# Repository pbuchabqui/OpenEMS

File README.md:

# OpenEMS

ECU para motores a combustao interna, focada no STM32H562RGT6 (Cortex-M33, C++17). Prioriza baixa latencia, baixo jitter e previsibilidade temporal para injecao, ignicao, sensores e calibracao.

Regras de codigo, gates de qualidade e errata: ver `CLAUDE.md`.

## Build

```bash
make firmware     # .elf/.hex/.bin em /tmp/openems-build
make host-test    # regressao no PC
make ci-local     # todos os gates antes de merge
make clean
```

## Instalacao no motor

Pelo dashboard proprio (`tools/openems_dash`, aba **Install**), com guia passo a passo; alternativa: TunerStudio com `tools/ts/openems.ini`.

## Documentacao

| Documento | Conteudo |
|---|---|
| `docs/bench_test_manual.md` | Teste de bancada na WeAct VGT6, sem atuadores |
| `docs/bench_report_template.md` | Modelo do relatório de bancada (preencher durante o ensaio) |
| `docs/hw/README.md` | Hardware e pinout |
| `docs/wiring_diagram.md` | Esquematicos eletricos |
| `docs/ROADMAP.md` | Backlog, progresso e histórico do que foi concluído |
| `docs/datalog.md` | Datalog em cartão SD (VGT6): formato, anel e ferramentas |
| `docs/nn_viabilidade.md` | Estudo: redes neurais no STM32H562 (X-τ, STFT, PID) |
| `docs/guia_instalacao.md` | Guia de instalação no motor (10 passos) |
| `docs/arquitetura.md` | Camadas, regras e contratos entre elas |
| `docs/pipeline_motor.md` | Captura CKP/CMP, combustível, ignição, scheduling, ADC, comunicação |
| `docs/errata_stm32h562.md` | Errata ES0565 e impactos no projeto |
| `docs/qualidade_e_testes.md` | Gates locais, layout dos testes host, segredos |
| `docs/mvp_bancada.md` | Definição de pronto da bancada, frames CAN, ETB, X-τ |
| `docs/estado_e_hardening.md` | Estado atual, hardening feito e pinout por placa |
| `docs/fueling_system.md`, `closed_loop_fuel.md`, `idle_system.md`, `ignition_system.md`, `protection_system.md`, `output_contract.md` | Subsistemas |

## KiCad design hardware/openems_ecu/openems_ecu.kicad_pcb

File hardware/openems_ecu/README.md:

# OpenEMS ECU — KiCad (fork mRE) — ⛔ CONGELADO

> **Não editar. Não é a board de produção.** Desde **2026-08-07** o desenho de produção
> é [`hardware/openems_v1/`](../openems_v1/), um projecto KiCad em branco.
> Porquê da mudança: [`docs/hw/microruseefi_as_base.md`](../../docs/hw/microruseefi_as_base.md).
>
> Isto fica por dois motivos: é o **recuo** se o desenho novo encalhar, e guarda as libs
> verificadas em `rusefi_lib/` (`tle8888qk.lib`, Net-Tie, AMPSEAL) que a board nova reutiliza.
>
> Estado em que ficou: DRC **nunca passou**, 2 camadas de sinal (a v1 pede 4), e restam
> nets fantasma do mRE (ex. `/PE1`, que no H562 LQFP100 é VCAP).

Cópia de trabalho a partir de [rusefi/hw_microRusEfi](https://github.com/rusefi/hw_microRusEfi),
adaptada ao firmware OpenEMS (**STM32H562VGT6** + **TLE8888-2QK**).

## Abrir

```bash
kicad hardware/openems_ecu/openems_ecu.kicad_pro
```

## Sheets

| Ficheiro | Função |
|----------|--------|
| `openems_ecu.kicad_sch` | Raiz hierárquica |
| `openems_ecu.kicad_pcb` | Layout (base mRE + rework H562) |
| `mcu_h562.kicad_sch` | MCU **STM32H562VGTx** LQFP100 (activo) |
| `stm32.kicad_sch` | Arquivo F407 — **não** está na hierarquia |
| `TLE8888-1QK.kicad_sch` | Hub TLE8888 |
| `TLE9201SG.kicad_sch` | ETB H-bridge mRE |
| `adc.kicad_sch` | Entradas analógicas |
| `hi-lo.kicad_sch` | USB / níveis |
| `pair.kicad_sch` | Low-sides (×2) |
| `FlashMemory.kicad_sch` | Flash opcional |

## Libs

| Caminho | Uso |
|---------|-----|
| `rusefi_lib/` | Símbolos legacy mRE (TLE, molex, …) |
| `rusefi_lib_external/` | Footprints / libs estendidas |
| `hellen-one` → `../vendor/hw_microRusEfi/hellen-one` | Footprint USB mini-B |

```bash
# Se libs faltarem após clone limpo:
git submodule update --init --recursive hardware/vendor/hw_microRusEfi
# rsync opcional a partir do vendor se rusefi_lib_external estiver incompleto
```

## Estado OpenEMS

1. ~~MCU H562 sheet~~ ✅ `mcu_h562.kicad_sch`, INJEN=`PE14`
2. ~~Rework 6 pads no PCB~~ ✅ VCAP×2, VDDUSB, VSSA/VSS; enables TLE→PE14/PE3
3. Auditoria TLE vs `docs/hw/tle8888_pinout.md`
4. Conector AMPSEAL 35+23 vs 48-pin mRE (aberto)
5. ETB TLE9201 vs BTS7960 (aberto)
6. DRC / refill zones / Gerber

Arquitectura: [`docs/hw/microruseefi_as_base.md`](../../docs/hw/microruseefi_as_base.md).

## Créditos

Hardware base © rusEFI / microRusEFI contributors.

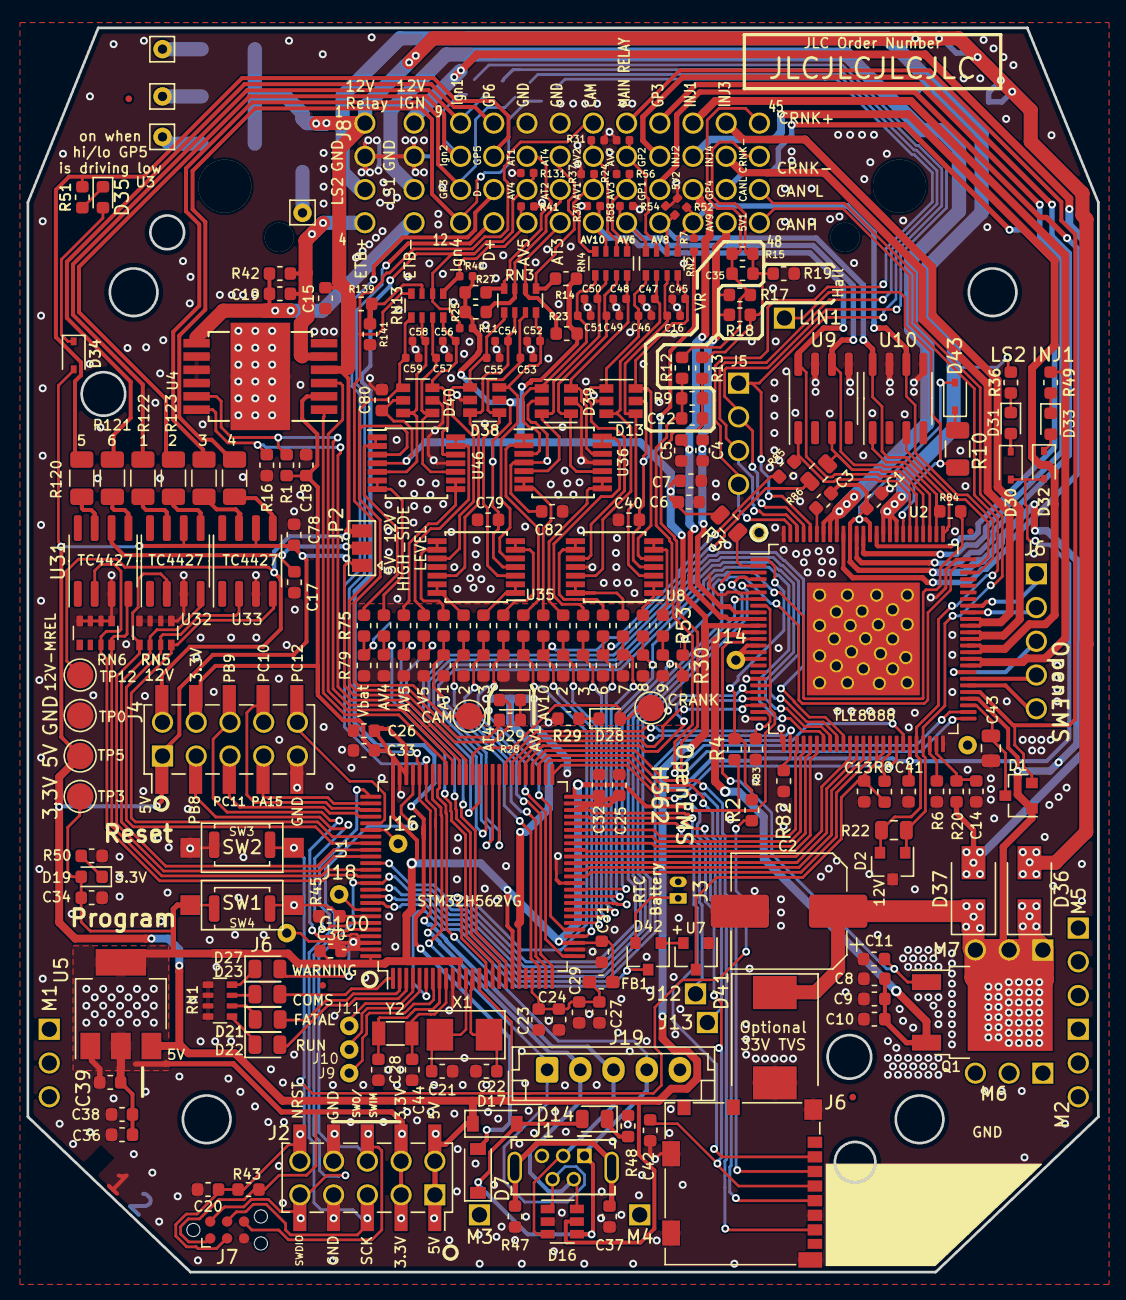
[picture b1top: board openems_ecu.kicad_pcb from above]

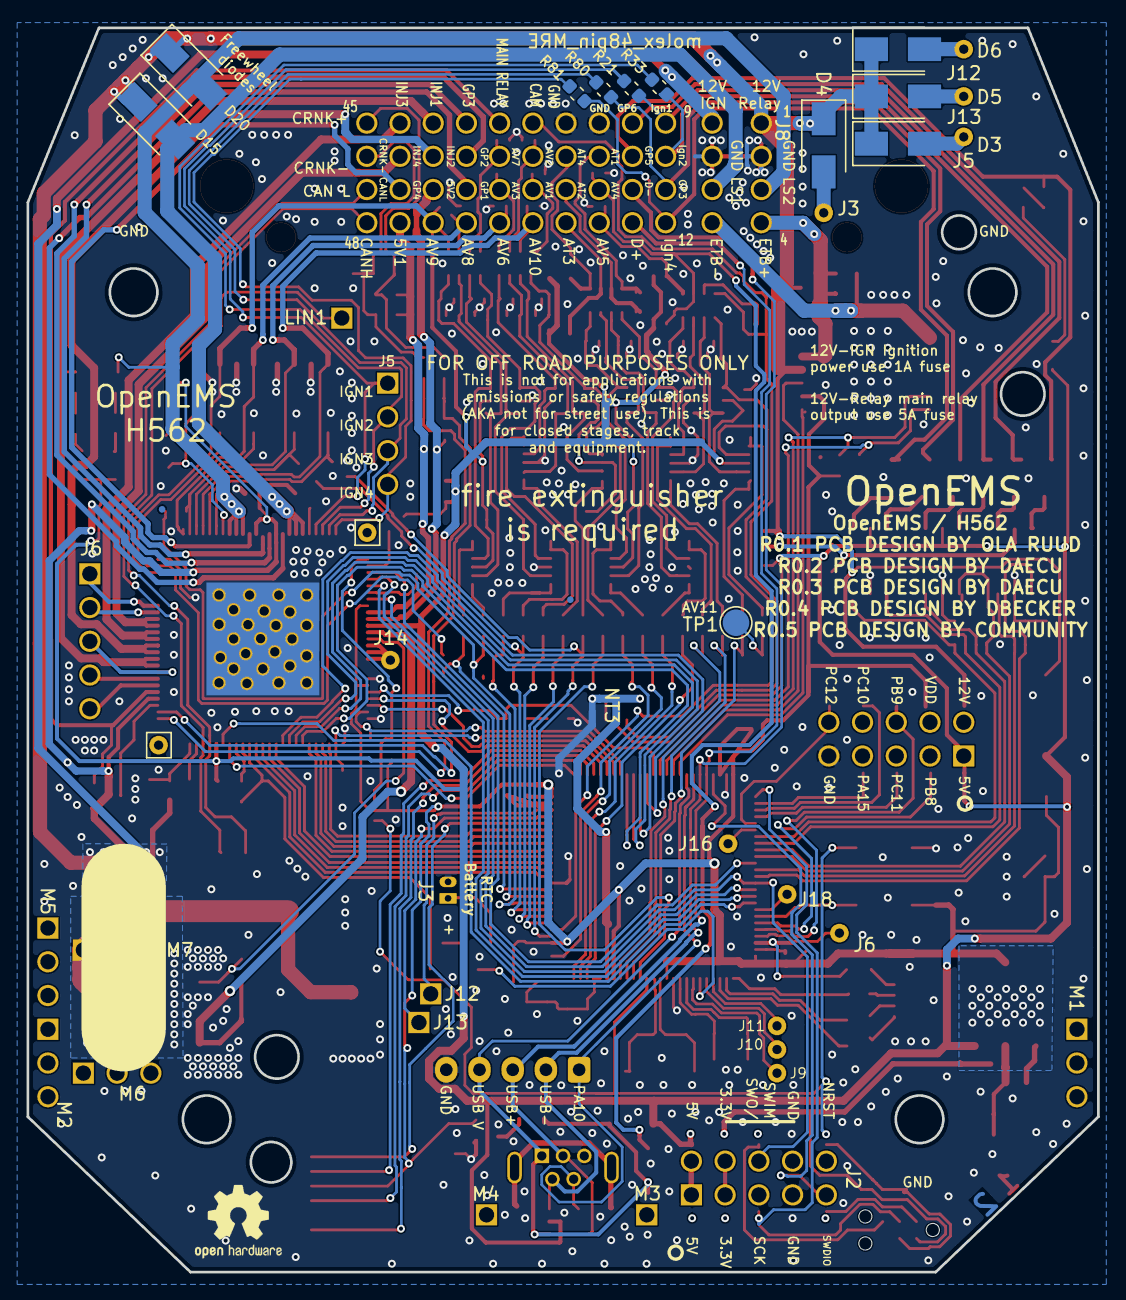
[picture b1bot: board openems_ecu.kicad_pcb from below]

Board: 2 copper layers, 80.6 x 93.7 mm, 254 parts (18 on the bottom side), 223 nets.

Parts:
C1, C6, C10, C13, C14, C15, C17, C18, C24, C30, C31, C32, C33, C34, C37, C38, C42, C78: 100nF; C_0603_1608Metric
C2: 100UF 50V; CP_Elec_8x10.5
C3, C11: 4.7nF; C_0603_1608Metric
C4, C5: 470nF; C_0603_1608Metric
C7, C8, C9: 10uF; C_0603_1608Metric
C12, C35: 1nF; C_0603_1608Metric
C16, C45, C46, C47, C48, C49, C50, C51, C52, C53, C54, C55, C56, C57, C58, C59: 100nF; C_0402_1005Metric
C19, C20, C29, C40, C79, C80, C82: 10nF; C_0603_1608Metric
C21, C22: 18pF; C_0603_1608Metric
C23, C27, C36: 1uF; C_0603_1608Metric
C25, C26, C41, C100: 2.2uF; C_0603_1608Metric
C28, C44: 6.8pF; C_0603_1608Metric
C39: 22uF; C_0603_1608Metric
C43: 22uF 25V; C_0805_2012Metric
D1, D42: BAV70; SOT-23
D2: PESD1CAN-UX; SOT-23
D3, D4, D5, D6, D15, D20, D36, D37: SS54; D_SMA
D7, D17: B5819W; D_SOD-123
D13, D16, D38, D39, D40: SRV05-4; SOT-23-6
D14, D22: LED-GREEN; LED_0805_2012Metric
D19, D28, D29, D31, D33, D35: LED-RED; LED_0603_1608Metric
D21: LED-RED; LED_0805_2012Metric
D23: LED-BLUE; LED_0805_2012Metric
D27: LED-YELLOW; LED_0805_2012Metric
D30, D32, D34, D43: 1N4148WS; D_SOD-323
D41: SM15T33C; D_SMC
FB1: FILTER; R_0603_1608Metric_Pad1.05x0.95mm_HandSolder
FID1, FID2, FID3, FID4, FID5, FID6: Fiducial; Fiducial_0.5mm_Mask1mm
G1: Disclaimer; Off_Road_Disclaimer
J1: USB_B_Mini; USB-MINI-B-VERTICAL
J2: Conn_02x05_Odd_Even; PinSocket_2x05_P2.54mm_Vertical_SMD
J3, J5, J12, J13, J15, J17: Conn_01x01; Pin_D0.7mm_L6.5mm_W1.8mm_FlatFork
J4: Conn_02x05_Counter_Clockwise; PinHeader_2x05_P2.54mm_Vertical_SMD
J6: Micro_SD_Card_Det; microSD_HC_Molex_104031-0811
J7: TC2030; Tag-Connect_TC2030-IDC-NL_2x03_P1.27mm_Vertical
J19: Conn_01x06; JST_EH_B5B-EH-A_1x05_P2.50mm_Vertical
JP2: High side voltage 5V 12V; SolderJumper-3_P1.3mm_Open_Pad1.0x1.5mm
LOGO1: DNP; OSHW-Logo2_7.3x6mm_SilkScreen
NT1, NT2: Net-Tie_2; Net-Tie_2_8.5mil
NT3: Analog Ground Net Tie; NetTie-2_SMD_Pad0.5mm
Q1: IPD30N06S2L-23; TO-252-2
R1, R4, R6, R12, R13, R16, R38, R39, R43, R44, R45, R46, R60, R61, R62, R63, R68, R69, R70, R71, R76, R77, R78, R79, R141: 10K; R_0603_1608Metric
R2: 0R DNP; R_0603_1608Metric
R3: 10K; R_0805_2012Metric
R5, R26, R32, R35, R53, R55, R57, R59, R64, R65, R66, R67, R72, R73, R74, R75: 6.8K; R_0603_1608Metric
R7, R11, R40: DNP; R_0402_1005Metric
R8, R21, R30, R33, R80, R81, R84, R85: 0R; R_0603_1608Metric
R9, R42, R82, R83: 4.7K; R_0603_1608Metric
R10: 1k; R_1206_3216Metric
R14, R20, R23, R25, R27: 2.7k; R_0603_1608Metric
R15, R17, R18, R19: DNP; R_0603_1608Metric
R22: 120; R_0805_2012Metric
R24, R31, R34, R37, R41, R52, R54, R56, R58, R131: 470K; R_0402_1005Metric
R28, R48: 2.2k; R_0603_1608Metric
R29, R36, R49, R50, R51: 1k; R_0603_1608Metric
R47: 100K; R_0603_1608Metric
R86: 0R; R_0805_2012Metric
R120, R121, R122, R123, R124, R125: 100; R_1206_3216Metric
R139: 39k; R_0603_1608Metric
RN1: 1k; R_Array_Convex_4x0603
RN2, RN3, RN4, RN5, RN6, RN13: 10k; R_Array_Convex_4x0603
SW1, SW2: SW_Push; SW_SPST_CK_RS282G05A3
SW3, SW4: SW_Push; SW_Push_SPST_NO_Alps_SKRK
TP0, TP3: GND; TestPoint_Pad_D2.0mm
TP1, TP2, TP4: TP; TestPoint_Pad_D2.0mm
TP5, TP12: 5V; TestPoint_Pad_D2.0mm
U1: STM32H562VGT6; LQFP-100_14x14mm_P0.5mm
U2: TLE8888QK; LQFP-100_14x14mm_P0.5mm_THERMAL
U3: molex_48pin_MRE; Molex_48_MRE
U4: TLE9201SG; Infineon_PG-DSO-12-11
U5: LM1117-3.3; SOT-223-3_TabPin2
U7: XC6206 3.3V; SOT-23
U8, U35, U36, U46: MCP6004; TSSOP-14_4.4x5mm_P0.65mm
U9, U10: VNLD5090; SO-8_3.9x4.9mm_P1.27mm
U31, U32, U33: MIC4427; SOIC-8_3.9x4.9mm_P1.27mm
X1: 8MHz 20pF; Crystal_SMD_5032-2Pin_5.0x3.2mm
Y2: 32768 Hz; Crystal_SMD_3215-2Pin_3.2x1.5mm

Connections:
/5V: C6.1, C7.1, C40.1, C41.1, C78.1, C79.1, C80.1, C82.1, D13.5, D16.5, D17.1 (K), D29.2 (A), D30.2 (A), D32.2 (A), D34.2 (A), D38.5, D39.5, D40.5, J2.1, J2.2, J4.1, JP2.1 (A), R3.2, R7.1, R11.2, R14.2, R23.2, R25.2, R27.2, R40.2, TP5.1, U2.11 (V5V), U2.45 (V5V_CAN), U3.J201, U3.J202, U3.J801, U5.3 (VI), U8.4 (V+), U32.6 (V+), U33.6 (V+), U35.4 (V+), U36.4 (V+), U46.4 (V+)
/5V1: C4.1, R17.1, R18.1, U2.9 (T5V1), U3.44
/5V2: C5.1, U2.10 (T5V2), U3.39
/12V_KEY: D37.2 (A), R20.2, U3.5
/12V_MREL: C15.1, D3.1 (K), D4.1 (K), D5.1 (K), D6.1 (K), D15.1 (K), D20.1 (K), D36.2 (A), J4.2, JP2.3 (B), R139.2, TP12.1, U3.1, U3.J802, U4.4 (VS)
/12V_SAFE: C1.1, C2.1, C3.1, D1.1 (A), D36.1 (K), D37.1 (K), D41.1 (A1), D43.2 (A), Q1.2 (D), U2.54 (BAT), U2.87 (BAT_PA), U2.90 (BAT_PB), U3.M71, U3.M72, U3.M73
/ADC/AGND: NT3.2, R38.1, R39.1, R44.1, R46.1, R60.1, R61.1, R62.1, R63.1, R68.1, R69.1, R70.1, R71.1, R76.1, R77.1, R78.1, R79.1, U1.20 (VSSA)
/ADC/AV11_MCU: R75.1, R79.2, TP1.1
/AT1: R27.1, RN3.4 (R4.1), U3.18
/AT1_MCU: R67.1, R71.2, U1.23 (PA0)
/AT2: R25.1, RN3.3 (R3.1), U3.23
/AT2_MCU: R66.1, R70.2, U1.24 (PA1)
/AT3: R23.1, RN3.2 (R2.1), U3.24
/AT3_MCU: R65.1, R69.2, U1.25 (PA2)
/AT4: R14.1, RN3.1 (R1.1), U3.22
/AT4_MCU: R64.1, R68.2, U1.26 (PA3)
/AV1: R37.1, RN4.4 (R4.1), U3.27
/AV1_MCU: R35.1, R46.2, U1.15 (PC0)
/AV2: R31.1, RN4.2 (R2.1), U3.26
/AV2_MCU: R26.1, R39.2, U1.31 (PA6)
/AV3: R24.1, RN4.1 (R1.1), U3.31
/AV3_MCU: R5.1, R38.2, U1.32 (PA7)
/AV4: D7.2 (A), R11.1, R131.1, RN13.2 (R2.1), U3.19
/AV4_MCU: R73.1, R77.2, U1.17 (PC2)
/AV5: R40.1, R41.1, RN13.1 (R1.1), U3.20
/AV5_MCU: R72.1, R76.2, U1.18 (PC3)
/AV6: R58.1, RN2.4 (R4.1), U2.78 (DFB_12), U3.32, U9.6 (D2)
/AV6_MCU: R59.1, R63.2, R86.2, U1.33 (PC4)
/AV7: R56.1, RN2.3 (R3.1), U3.30
/AV7_MCU: R57.1, R62.2, U1.34 (PC5)
/AV8: R54.1, RN2.2 (R2.1), U2.76 (DFB_11), U3.36, U10.8 (D1)
/AV8_MCU: R55.1, R61.2, R84.2, U1.35 (PB0)
/AV9: R7.2, R52.1, RN2.1 (R1.1), U2.73 (DFB10), U3.40, U10.6 (D2)
/AV9_MCU: R30.2, R53.1, R60.2, U1.36 (PB1)
/AV10: R34.1, RN4.3 (R3.1), U2.80 (DFB_13), U3.28, U9.8 (D1)
/AV10_MCU: R32.1, R44.2, R85.2, U1.29 (PA4)
/CAM_MCU: C59.1, D40.4, RN13.5 (R4.2), TP2.1, U1.30 (PA5), U46.3 (+)
/CAM_SENSOR: R28.1, RN13.4 (R4.1), U3.25
/CANH: D2.2 (C2), R22.1, U2.46 (CAN_H), U3.48
/CANL: D2.1 (C1), R22.2, U2.47 (CAN_L), U3.47
/CRANK: D28.2 (A), TP4.1, U1.63 (PC6), U2.21 (VR_OUT)
/CRNK+: C35.1, R12.1, R15.1, R17.2, U3.45
/CRNK-: C35.2, R13.1, R15.2, R18.2, R19.2, U3.46
/CS_TLE: U1.86 (PD5), U2.3 (CSN)
/E-THROTTLE+: C19.2, R42.2, U3.4, U4.5 (OUT1)
/E-THROTTLE-: C19.1, R42.1, U3.8, U4.7 (OUT2)
/FlashMemory/CS: J6.2 (DAT3/CD), U1.46 (PE15)
/FlashMemory/SCK: J6.5 (CLK), U1.52 (PB13)
/FlashMemory/SI: J6.3 (CMD), U1.54 (PB15)
/FlashMemory/SO: J6.7 (DAT0), U1.53 (PB14)
/GP1: U2.91 (OUT_21), U3.35
/GP2: U2.89 (OUT_22), U3.34
/GP3: U2.88 (OUT_23), U3.33
/GP4: U2.86 (OUT_24), U3.43
/GP5: R51.2, R120.1, U3.14
/GP6: R121.1, U3.13
/H-BRIDGE/DIR: U1.67 (PA8), U4.1 (DIR)
/H-BRIDGE/DIS: R1.2, U1.65 (PC8), U4.11 (DIS)
/H-BRIDGE/PWM: R16.1, U1.64 (PC7), U4.12 (PWM)
/H-BRIDGE/SO: U1.66 (PC9), U4.3 (SO)
/INJECTOR-1: R49.2, U2.59 (OUT_1A), U2.60 (OUT_1B), U3.37
/INJECTOR-2: U2.61 (OUT_2A), U2.62 (OUT_2B), U3.38
/INJECTOR-3: U2.63 (OUT_3A), U2.64 (OUT_3B), U3.41
/INJECTOR-4: U2.65 (OUT_4A), U2.66 (OUT_4B), U3.42
/Ign1: R21.1, R122.1, U3.9
/Ign2: R33.1, R123.1, U3.10
/Ign3: R80.1, R124.1, U3.11
/Ign4: R81.1, R125.1, U3.12
/LINBUS: R10.2, U2.82 (LIN_IO), U3.LIN1
/LS1: D15.2 (A), U2.92 (OUT_6A), U2.93 (OUT_6B), U2.94 (OUT_6C), U3.7
/LS2: D20.2 (A), R36.2, U2.83 (OUT_5A), U2.84 (OUT_5B), U2.85 (OUT_5C), U3.3
/MAIN_RELAY: D1.2 (A), U2.55 (MR), U3.29
/MCU/BOOT0: R45.1, SW1.2, SW4.2, U1.94 (BOOT0)
/MCU/PA9: D7.1 (K), D14.2 (A), D16.4, D17.2 (A), J1.1 (VBUS), J19.4, NT1.2
/MCU/PA10: D16.1, J1.4 (ID), J19.1, U1.69 (PA10)
/MCU/PA13: J2.9, J7.2, U1.72 (PA13), U3.J209
/MCU/PA14: J2.5, J7.4, U1.76 (PA14), U3.J205
/MCU/PB2-BOOT1: NT2.2, U1.37 (PB2)
/MCU/PB6: U1.92 (PB6), U2.44 (CAN_TX)
/MCU/PB7: U1.93 (PB7), U3.J18
/MCU/PB12: U1.51 (PB12), U2.43 (CAN_RX)
/MCU/PD0: U1.81 (PD0), U3.J16
/MCU/PD1: RN5.8 (R1.2), U1.82 (PD1), U33.4 (IN_B)
/MCU/PD2: RN5.7 (R2.2), U1.83 (PD2), U33.2 (IN_A)
/MCU/PD3: RN5.6 (R3.2), U1.84 (PD3), U32.4 (IN_B)
/MCU/PD4: RN5.5 (R4.2), U1.85 (PD4), U32.2 (IN_A)
/MCU/PD6: RN6.8 (R1.2), U1.87 (PD6), U31.4 (IN_B)
/MCU/PD7: RN6.7 (R2.2), U1.88 (PD7), U31.2 (IN_A)
/MCU/PD8: U1.55 (PD8), U2.22 (LIN_TX)
/MCU/PD9: U1.56 (PD9), U2.23 (LIN_RX)
/MCU/PD10: R82.1, U1.57 (PD10), U2.27 (IGN_EN)
/MCU/PD11: R83.1, U1.58 (PD11), U2.24 (INJ_EN)
/MCU/PE5: U1.4 (PE5), U3.J11
/MCU/PE6: U1.5 (PE6), U3.J10
/MCU/PE7: U1.38 (PE7), U2.39 (IN_12)
/MCU/PE8: U1.39 (PE8), U2.38 (IN_11)
/MCU/PE9: U1.40 (PE9), U2.37 (IN_10)
/MCU/PE10: U1.41 (PE10), U2.36 (IN_9)
/MCU/PE11: U1.42 (PE11), U2.31 (IN_4)
/MCU/PE12: U1.43 (PE12), U2.30 (IN_3)
/MCU/PE13: U1.44 (PE13), U2.29 (IN_2)
/MCU/PE14: U1.45 (PE14), U2.28 (IN_1)
/MCU/VBAT: D42.1 (A), U7.2 (VO)
/MCU/VCAP_PB11: C25.1, U1.48 (PB11)
/MCU/VCAP_PE1: C100.1, U1.98 (PE1)
/MCU/VDDA: C23.2, C24.2, C27.2, C29.2, FB1.2, U1.21 (VREF+), U1.22 (VDDA)
/MCU/Vrtc: D42.2 (A), U3.J31
/MCU/Vrtcc: D42.3 (K), U1.6 (VBAT)
/MCU/shield: C37.1, J1.6 (Shield), R47.1
/PA15: J4.7, U1.77 (PA15), U3.J807
/PB8: J4.3, U1.95 (PB8), U3.J803
/PB9: J4.6, U1.96 (PB9), U3.J806
/PB10: U1.47 (PB10), U3.J13
/PC10: J4.8, U1.78 (PC10), U3.J808
/PC11: J4.5, U1.79 (PC11), U3.J805
/PC12: J4.10, U1.80 (PC12), U3.J810
/PC13: U1.7 (PC13), U3.J9
/PD12: U1.59 (PD12), U2.32 (IN_5)
/PD13: U1.60 (PD13), U2.33 (IN_6)
/PD14: U1.61 (PD14), U2.34 (IN_7)
/PD15: U1.62 (PD15), U2.35 (IN_8)
/PE0: U1.97 (PE0), U3.J6
/PE2: D23.2 (A), U1.1 (PE2)
/PE3: D21.2 (A), U1.2 (PE3)
/PE4: D22.2 (A), U1.3 (PE4)
/RST: C20.2, J2.10, J7.3, R2.2, R43.2, SW2.1, SW3.1, U1.14 (NRST), U3.J210
/SCK: J2.6, J7.6, U1.89 (PB3), U2.7 (FCLP), U3.J206
/SI: U1.91 (PB5), U2.5 (SIP)
/SO: U1.90 (PB4), U2.4 (SDO)
/TLE8888-1QK/5V_STBY: C13.1, R8.1, U2.40 (EO_TIMER), U2.41 (V5V_STBY), U7.3 (VI)
/TLE8888-1QK/BAT_STBY: C43.1, D1.3 (K), U2.53 (BAT_STBY)
/TLE8888-1QK/IGN_OUT_1: R21.2, U2.96 (IGN_1), U3.J51
/TLE8888-1QK/IGN_OUT_2: R33.2, U2.97 (IGN_2), U3.J52
/TLE8888-1QK/IGN_OUT_3: R80.2, U2.98 (IGN_3), U3.J53
/TLE8888-1QK/IGN_OUT_4: R81.2, U2.99 (IGN_4), U3.J54
/TLE8888-1QK/KEY: C14.1, R20.1, U2.49 (KEY)
/TLE8888-1QK/OUT_7: U2.14 (0UT_7A), U2.15 (OUT_7B), U2.16 (OUT_7C), U3.J14
/TLE8888-1QK/OUT_14: U2.68 (OUT_14), U3.J61
/TLE8888-1QK/OUT_15: U2.67 (OUT_15), U3.J62
/TLE8888-1QK/OUT_16: U2.58 (OU716), U3.J63
/TLE8888-1QK/OUT_17: U2.57 (OUT_17), U3.J64
/TLE8888-1QK/OUT_18: U2.56 (OUT_18), U3.J65
/TLE8888-1QK/RST: R2.1, R4.2, U2.1 (RST)
/TLE8888-1QK/TLE_MON: R3.1, U2.2 (MON)
/TLE8888-1QK/V6GATE: C11.1, Q1.1 (G), U2.13 (VG)
/TLE8888-1QK/V6V: C8.1, C9.1, C10.1, Q1.3 (S), U2.12 (V6V)
/TLE8888-1QK/VR+: C12.1, R9.1, R12.2, U2.52 (VR_IN_1)
/TLE8888-1QK/VR-: C12.2, R9.2, R13.2, U2.51 (VR_IN_2)
/TLE8888-1QK/WAKE: R6.2, U2.48 (WAKE)
/TLE_OUT10_PRE: R30.1, U2.74 (OUT_10), U10.3 (IN2)
/TLE_OUT11_PRE: R84.1, U2.77 (OUT_11), U10.1 (IN1)
/TLE_OUT12_PRE: R86.1, U2.79 (OUT_12), U9.3 (IN2)
/TLE_OUT13_PRE: R85.1, U2.81 (OUT_13), U9.1 (IN1)
/USB_D+: D16.3, J1.3 (D+), J19.3, U1.71 (PA12), U3.16
/USB_D-: D16.6, J1.2 (D-), J19.2, U1.70 (PA11), U3.15
/VDD: C18.1, C26.1, C30.2, C31.2, C32.2, C33.2, C34.2, C36.2, C38.1, C39.2, C42.1, D19.2 (A), FB1.1, J2.3, J2.4, J4.4, J6.4 (VDD), J7.1, R1.1, R4.1, R43.1, SW1.1, SW4.1, TP3.1, U1.11 (VDD), U1.28 (VDD), U1.50 (VDD), U1.73 (VCAP_2), U1.75 (VDD), U1.100 (VDD), U2.8 (FCLN), U2.20 (VDD_IO), U3.J203, U3.J204, U3.J804, U4.2 (VSO), U5.2 (VO)
/Vbat_MCU: R74.1, R78.2, U1.16 (PC1)
GND: C1.2, C2.2, C4.2, C5.2, C6.2, C7.2, C8.2, C9.2, C10.2, C11.2, C13.2, C14.2, C15.2, C16.2, C17.2, C18.2, C20.1, C21.2, C22.2, C23.1, C24.1, C25.2, C26.2, C27.1, C28.2, C29.1, C30.1, C31.1, C32.1, C33.1, C34.1, C36.1, C37.2, C38.2, C39.1, C40.2, C41.2, C42.2, C43.2, C44.1, C45.2, C46.2, C47.2, C48.2, C49.2, C50.2, C51.2, C52.2, C53.2, C54.2, C55.2, C56.2, C57.2, C58.2, C59.2, C78.2, C79.2, C80.2, C82.2, C100.2, D2.3 (C3), D13.2, D16.2, D38.2, D39.2, D40.2, D41.2 (A2), J1.5 (GND), J2.7, J2.8, J4.9, J6.6 (VSS), J6.11 (SHIELD), J7.5, J19.5, NT2.1, NT3.1, R6.1, R16.2, R19.1, R24.2, R29.2, R31.2, R34.2, R37.2, R41.2, R45.2, R47.2, R48.1, R50.1, R52.2, R54.2, R56.2, R58.2, R82.2, R83.2, R131.2, R141.2, RN1.5 (R4.2), RN1.6 (R3.2), RN1.7 (R2.2), RN1.8 (R1.2), RN5.1 (R1.1), RN5.2 (R2.1), RN5.3 (R3.1), RN5.4 (R4.1), RN6.1 (R1.1), RN6.2 (R2.1), RN6.3 (R3.1), RN6.4 (R4.1), SW2.2, SW3.2, TP0.1, U1.10 (VSS), U1.19 (VDD), U1.27 (VSS), U1.49 (VCAP_1), U1.74 (VSS), U1.99 (VSS), U2.6 (SIN), U2.19 (NC), U2.25 (PGND), U2.26 (KEY_OFF_DLY), U2.50 (PGND), U2.75 (PGND), U2.100 (AGND), U2.101 (GND), U3.2, U3.6, U3.17, U3.21, U3.J32, U3.J207, U3.J208, U3.J809, U4.6 (GND), U4.8 (SI), U4.9 (CSN), U4.10 (SCK), U4.13 (GND), U5.1 (GND), U7.1 (GND), U8.11 (V-), U9.5 (S2), U9.7 (S1), U10.5 (S2), U10.7 (S1), U31.3 (GND), U32.3 (GND), U33.3 (GND), U35.11 (V-), U36.11 (V-), U46.11 (V-)
unnamed: C3.2, U2.95 (CP)
unnamed: C16.1, D13.6, RN2.8 (R1.2), U8.5 (+)
unnamed: C17.1, JP2.2 (C), U31.6 (V+)
unnamed: C21.1, U1.12 (PH0), X1.2
unnamed: C22.1, U1.13 (PH1), X1.1
unnamed: C28.1, U1.8 (PC14), Y2.1
unnamed: C44.2, U1.9 (PC15), Y2.2
unnamed: C45.1, D13.4, RN2.7 (R2.2), U8.3 (+)
unnamed: C46.1, D13.3, RN2.6 (R3.2), U8.12 (+)
unnamed: C47.1, D13.1, RN2.5 (R4.2), U8.10 (+)
unnamed: C48.1, D39.3, RN4.8 (R1.2), U36.12 (+)
unnamed: C49.1, D39.1, RN4.7 (R2.2), U36.10 (+)
unnamed: C50.1, D39.6, RN4.6 (R3.2), U36.5 (+)
unnamed: C51.1, D39.4, RN4.5 (R4.2), U36.3 (+)
unnamed: C52.1, D38.6, RN3.8 (R1.2), U35.5 (+)
unnamed: C53.1, D38.4, RN3.7 (R2.2), U35.3 (+)
unnamed: C54.1, D38.3, RN3.6 (R3.2), U35.12 (+)
unnamed: C55.1, D38.1, RN3.5 (R4.2), U35.10 (+)
unnamed: C56.1, D40.3, RN13.8 (R1.2), U46.12 (+)
unnamed: C57.1, D40.1, RN13.7 (R2.2), U46.10 (+)
unnamed: C58.1, D40.6, RN13.6 (R3.2), U46.5 (+)
unnamed: D3.2 (A), J5.1
unnamed: D4.2 (A), J3.1
unnamed: D5.2 (A), J13.1
unnamed: D6.2 (A), J12.1
unnamed: D14.1 (K), R48.2
unnamed: D19.1 (K), R50.2
unnamed: D21.1 (K), RN1.2 (R2.1)
unnamed: D22.1 (K), RN1.1 (R1.1)
unnamed: D23.1 (K), RN1.3 (R3.1)
unnamed: D27.1 (K), RN1.4 (R4.1)
unnamed: D28.1 (K), R29.1
unnamed: D29.1 (K), R28.2
unnamed: D30.1 (K), D31.2 (A)
unnamed: D31.1 (K), R36.1
unnamed: D32.1 (K), D33.2 (A)
unnamed: D33.1 (K), R49.1
unnamed: D34.1 (K), D35.2 (A)
unnamed: D35.1 (K), R51.1
unnamed: D43.1 (K), R10.1
unnamed: NT1.1, U1.68 (PA9)
unnamed: R5.2, U36.13 (-), U36.14
unnamed: R8.2, U2.42 (CAN_WKEN)
unnamed: R26.2, U36.8, U36.9 (-)
unnamed: R32.2, U36.6 (-), U36.7
unnamed: R35.2, U36.1, U36.2 (-)
unnamed: R53.2, U8.6 (-), U8.7
unnamed: R55.2, U8.1, U8.2 (-)
unnamed: R57.2, U8.13 (-), U8.14
unnamed: R59.2, U8.8, U8.9 (-)
unnamed: R64.2, U35.6 (-), U35.7
unnamed: R65.2, U35.1, U35.2 (-)
unnamed: R66.2, U35.13 (-), U35.14
unnamed: R67.2, U35.8, U35.9 (-)
unnamed: R72.2, U46.13 (-), U46.14
unnamed: R73.2, U46.8, U46.9 (-)
unnamed: R74.2, U46.6 (-), U46.7
unnamed: R75.2, U46.1, U46.2 (-)
unnamed: R120.2, U31.7 (OUT_A)
unnamed: R121.2, U31.5 (OUT_B)
unnamed: R122.2, U32.7 (OUT_A)
unnamed: R123.2, U32.5 (OUT_B)
unnamed: R124.2, U33.7 (OUT_A)
unnamed: R125.2, U33.5 (OUT_B)
unnamed: R139.1, R141.1, RN13.3 (R3.1)

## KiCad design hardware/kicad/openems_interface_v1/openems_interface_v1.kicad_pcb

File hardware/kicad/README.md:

# OpenEMS — KiCad hardware

## Caminho de fabrico (activo)

**Projecto:** [`../openems_ecu/openems_ecu.kicad_pro`](../openems_ecu/openems_ecu.kicad_pro)  
**Base:** microRusEFI (`hardware/vendor/hw_microRusEfi`)  
**Arquitectura:** [`../../docs/hw/microruseefi_as_base.md`](../../docs/hw/microruseefi_as_base.md)

```bash
kicad hardware/openems_ecu/openems_ecu.kicad_pro
```

| Area | State |
|------|--------|
| Cópia de trabalho a partir do mRE | ✅ |
| TLE8888 no esquemático/PCB vendor | ✅ (auditar) |
| MCU H562 soldado | ❌ sheet a criar |
| Conector / ETB OpenEMS | ⏳ decisões abertas |
| Fab | ❌ só após adaptação + DRC |

## Scaffold experimental (NÃO fabricar)

**Projecto:** `openems_interface_v1/` — útil para pinmap/docs e protótipo de hierarquia.  
**Não** é o caminho de fabrico. Ver `openems_interface_v1/LEIA-ME.md`.

Scripts `layout_clean.py` / `build_all.sh` **não** geram a PCB de produção.

## Hellen-One

**Não** usado como base da ECU OpenEMS. Módulos oficiais não têm TLE8888 nem H562.  
Pode voltar a ser considerado mais tarde só para adaptadores PnP por veículo.

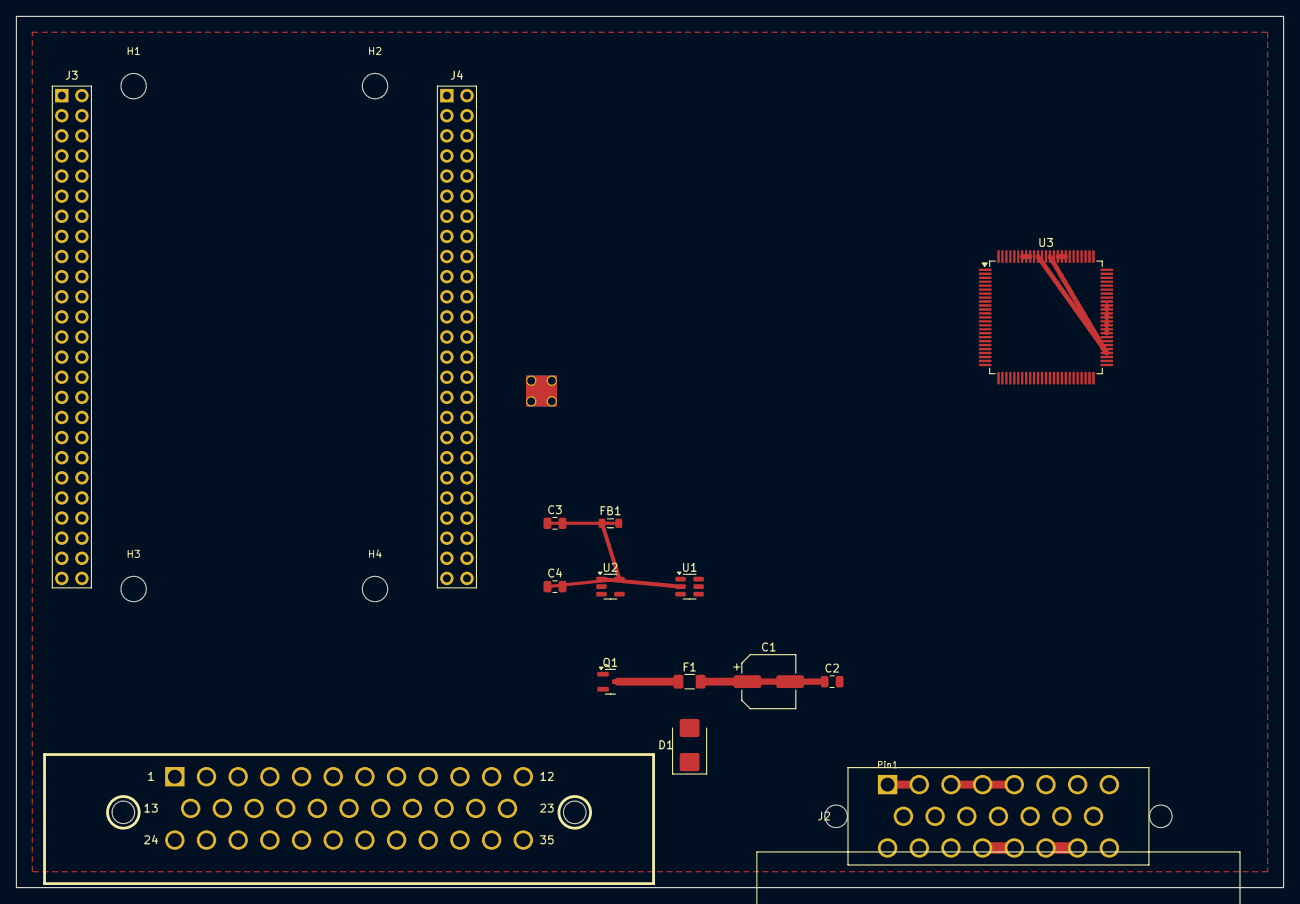
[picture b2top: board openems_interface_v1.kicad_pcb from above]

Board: 2 copper layers, 160.0 x 110.0 mm, 20 parts (0 on the bottom side), 49 nets.

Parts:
C1: CP_Elec_6.3x5.8
C2, C3, C4: C_0805_2012Metric
D1: D_SMB
F1: Fuse_1206_3216Metric
FB1: L_0805_2012Metric
H1, H2, H3, H4: M3; 3.2mm
J1: 776180; rusEFI_AMPSEAL_35_RA_776180
J2: TE_770669_AMPSEAL_23_RA
J3, J4: WeAct_PinHeader_2x25_P2.54mm
NT1: NetTie-4_THT_Pad1.0mm
Q1: SOT-23
U1: SOT-23-6
U2: SOT-23-5
U3: LQFP-100_14x14mm_P0.5mm

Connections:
+3V3: C4.1, FB1.1, U2.5, U3.8, U3.20
+5V_MAIN: U1.2, U1.4, U1.6, U2.1, U2.3
+5V_SENS_A: J1.16, U3.9
+5V_SENS_B: J1.17, U3.10
AGND: C3.2, C4.2, J3.5, NT1.3, U2.2, U2.4, U3.6, U3.100
CANH: J1.20, U3.46
CANL: J1.21, U3.47
CKP_N: J1.2, U3.51
CKP_P: J1.1, U3.52
ETB_MOTOR_N: J2.21, J2.22
ETB_MOTOR_P: J2.19, J2.20
FAN_RLY: J2.17, U3.67
IGN1: J2.10, U3.96
IGN2: J2.11, U3.97
IGN3: J2.12, U3.98
IGN4: J2.13, U3.99
INJ1: J2.6, U3.59, U3.60
INJ2: J2.7, U3.61, U3.62
INJ3: J2.8, U3.63, U3.64
INJ4: J2.9, U3.65, U3.66
MAIN_RLY: J2.18, U3.55
MCU_PA0: J3.7, U3.21
MCU_PB6: J4.11, U3.38
MCU_PB7: J4.12, U3.39
MCU_PB8: J4.9, U3.43
MCU_PB9: J4.10, U3.44
MCU_PB12: J3.29, U3.3
MCU_PB13: J3.30, U3.7
MCU_PB14: J3.31, U3.4
MCU_PB15: J3.32, U3.5
MCU_PE0: J4.7, U3.28
MCU_PE2: J4.5, U3.29
MCU_PE3: J4.6, U3.27
MCU_PE4: J4.3, U3.30
MCU_PE6: J4.2, U3.31
MCU_PE9: J3.22, U3.32
MCU_PE10: J3.23, U3.36
MCU_PE11: J3.24, U3.33
MCU_PE12: J3.25, U3.37
MCU_PE13: J3.26, U3.34
PGND: C1.2, C2.2, D1.1, J2.3, J2.4, J2.5, NT1.1, U1.1, U3.25, U3.50, U3.75
PUMP_RLY: J2.16, U3.68
SGND: J1.18, J1.19, NT1.2
SHIELD_GND: J1.3, J1.22, J1.27, NT1.4
VBAT: C1.1, C2.1, D1.2, F1.1, F1.2, Q1.3, U1.3, U1.5, U3.54, U3.87, U3.90
VBAT_RAW: J2.1, J2.2, Q1.1, Q1.2
VDDA: C3.1, FB1.2
VVT_EXH: J2.14, U3.83, U3.84, U3.85
VVT_INT: J2.15, U3.92, U3.93, U3.94

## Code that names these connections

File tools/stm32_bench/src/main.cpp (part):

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 *
 *   Gerador   ECU       Função
 *   ────────  ────────  ────────────────────────────────────────────
 *   PA0   →   PA0       CKP (60-2)   TIM5_CH1 AF2, toggle por compare
 *   PA1   →   PA1       CMP (1/720°) TIM5_CH2 AF2, toggle por compare
 *   PA4   →   PA3       MAP  (DAC1_OUT1, direto)
 *   PA5   →   PA4       TPS  (DAC1_OUT2, direto)
 *   PA6   →   PB0       CLT  (TIM3_CH1 PWM + RC)
 *   PA7   →   PB1       IAT  (TIM3_CH2 PWM + RC)
 *   PB0   →   PC0       APP1 (TIM3_CH3 PWM + RC)
 *   PB1   →   PC1       OIL  (TIM3_CH4 PWM + RC)
 *   PB6   →   PC4       FUEL (TIM4_CH1 PWM + RC)
 *   PB7   →   PA2       ETB TPS1 (TIM4_CH2 PWM + RC)
 *   PB8   →   PC5       ETB TPS2, invertido (TIM4_CH3 PWM + RC)
 *   PC0   ←   PE9       IGN1        PC4   ←   PE0        INJ1
 *   PC1   ←   PE11      IGN2        PC5   ←   PE2        INJ2
 *   PC2   ←   PE13      IGN3        PB12  ←   PE4        INJ3
 *   PC3   ←   PE15      IGN4        PB13  ←   PE6        INJ4
 *   GND   —   GND       OBRIGATÓRIO
 *
 *   Se a ECU sob teste for BOARD=rgt6: INJ PA15/PB3/PC10/PC11, IGN PC6-PC9.
 *   Entradas do scope usam EXTI (um número de pino por linha: 0-5, 12, 13).
 *   Pinos, AF e DAC: docs do datasheet em docs/alternatefunctions2.pdf.
 *
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// ── SECÇÃO 1 — Base de tempo (TIM5, 32 bits, 1 MHz) e gerador CKP/CMP
// ═══════════════════════════════════════════════════════════════════════════

// PA0/PA1 sem ALT1 resolvem para TIM2 no pinmap do core; TIM5_CH1/CH2 (AF2) exigem ALT1.
static constexpr uint32_t kCkpPin    = PA0_ALT1;   // TIM5_CH1 AF2
static constexpr uint32_t kCmpPin    = PA1_ALT1;   // TIM5_CH2 AF2
static constexpr uint32_t kTickHz    = 1000000u;
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// exato da borda (valor de CCR), sem fio de loopback.

struct ChanDef {
    uint32_t    gpio;      // pino Arduino (PC0...) ou kVirtual
    const char  name[6];
    const char  pin[6];    // pino da ECU sob teste (VGT6)
    const char  gpio_name[5];
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static constexpr uint32_t kVirtual = 0xFFFFFFFFu;

static ChanDef kChan[] = {
    { PC0,  "IGN1", "PE9",  "PC0",  true  },   // CH0 — IGN1 (cyl 1)
    { PC1,  "IGN2", "PE11", "PC1",  true  },   // CH1 — IGN2 (cyl 2)
    { PC2,  "IGN3", "PE13", "PC2",  true  },   // CH2 — IGN3 (cyl 3)
    { PC3,  "IGN4", "PE15", "PC3",  true  },   // CH3 — IGN4 (cyl 4)
    { PC4,  "INJ1", "PE0",  "PC4",  true  },   // CH4 — INJ1 (cyl 1)
    { PC5,  "INJ2", "PE2",  "PC5",  true  },   // CH5 — INJ2 (cyl 2)
    { PB12, "INJ3", "PE4",  "PB12", true  },   // CH6 — INJ3 (cyl 3)
    { PB13, "INJ4", "PE6",  "PB13", true  },   // CH7 — INJ4 (cyl 4)
    { kVirtual, "CKP", "PA0", "-",  true  },   // CH8 — virtual, da ISR do gerador
    { kVirtual, "CMP", "PA1", "-",  true  },   // CH9 — virtual, da ISR do gerador
};
static constexpr int kNChan = (int)(sizeof(kChan) / sizeof(kChan[0]));
static constexpr int kCkpChan = 8;  // índice do canal CKP
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// ── SECÇÃO 3 — Gerador CKP/CMP (TIM5 CH1/CH2, OC toggle, borda em hardware)
// ═══════════════════════════════════════════════════════════════════════════
//
// CH1 alterna PA0 no match de CCR1; a ISR só carrega o próximo CCR1 (≥55 µs à frente
// a 9000 rpm). A borda é do hardware: o jitter de ISR não aparece no pino, desde que a
// latência fique abaixo de meio dente (TIM5 tem prioridade 0).
// CH2 gera o CMP: 1 µs depois da borda do CKP do dente kCmpTooth da volta 0 (mesmo
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// ── SECÇÃO 4 — Sensores analógicos (DAC1 + PWM com filtro RC)
// ═══════════════════════════════════════════════════════════════════════════

// MAP/TPS: DAC1 de 12 bits (OUT1=PA4, OUT2=PA5), ligação direta ao ADC da ECU.
// Os trims abaixo estão neutros: calibre na bancada com multímetro (DAC1/DAC2 <0-4095>)
// e a leitura na ECU. O buffer de saída do DAC pode não chegar aos trilhos; confirmar
// nas características elétricas do DAC (DS14138) e ajustar os trims.
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
static void dac_init_map_tps() {
    __HAL_RCC_DAC1_CLK_ENABLE();
    pinMode(PA4, INPUT_ANALOG);
    pinMode(PA5, INPUT_ANALOG);
    DAC1->CR |= DAC_CR_EN1 | DAC_CR_EN2;
    delay(1);   // tWAKEUP
}
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
struct PwmChan { uint32_t pin; TIM_TypeDef* tim; uint8_t ch; const char* name; HardwareTimer* ht; };
static PwmChan kPwm[] = {
    { PA6, TIM3, 1, "CLT",  nullptr },
    { PA7_ALT1, TIM3, 2, "IAT",  nullptr },   // sem ALT1 seria TIM1_CH1N
    { PB0_ALT1, TIM3, 3, "APP",  nullptr },
    { PB1_ALT1, TIM3, 4, "OIL",  nullptr },
    { PB6, TIM4, 1, "FUEL", nullptr },
    { PB7, TIM4, 2, "ETB1", nullptr },
    { PB8, TIM4, 3, "ETB2", nullptr },
};
static constexpr int kNPwm = (int)(sizeof(kPwm) / sizeof(kPwm[0]));

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        const float pw   = m.pw_us    / 1000.0f;
        const float per  = m.period_us / 1000.0f;
        const float freq = (m.period_us > 0) ? 1e6f / m.period_us : 0.0f;
        const char* src  = (ch == kCkpChan) ? "PA0*" : kChan[ch].pin;
        Serial.printf("│%2d│%-6s│%-7s│%8.3f│%8.3f│%8.2f│%7lu│%s│\n",
                      ch, kChan[ch].name, src,
                      pw, per, freq, m.pulse_count,
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    else if (strcmp(cmd, "WOT")    == 0)   preset_wot();
    else if (strcmp(cmd, "COAST")  == 0)   preset_coast();
    else if (strcmp(cmd, "DAC1") == 0 && has_val) {
        // Código cru no DAC1_OUT1 (PA4, MAP) para medir com multímetro
        const int code = constrain(val, 0, 4095);
        dac_write_map((uint16_t)code);
        Serial.printf("  [DAC] PA4=%d (%.3fV esperado)\n", code, code * 3.3f / 4095.0f);
    }
    else if (strcmp(cmd, "DAC2") == 0 && has_val) {
        const int code = constrain(val, 0, 4095);
        dac_write_tps((uint16_t)code);
        Serial.printf("  [DAC] PA5=%d (%.3fV esperado)\n", code, code * 3.3f / 4095.0f);
    }
    else if (strcmp(cmd, "STATUS") == 0)   print_status();
}
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
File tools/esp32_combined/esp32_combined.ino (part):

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 *
 *   ESP32 GPIO  STM32      Função
 *   ──────────  ─────────  ────────────────────
 *   GPIO 2  →  PA0        CKP output (60-2, RMT hardware)
 *   GPIO 4  →  PA1        CMP output (1 pulso/720°, RMT hardware)
 *   GPIO 2  →  GPIO34     Wire loopback p/ scope CKP (mesma placa)
 *   GPIO 32 ←  PE9        IGN1
 *   GPIO 33 ←  PE11       IGN2
 *   GPIO 26 →  PA3        MAP  (DAC2 real, 8-bit, ligação DIRETA sem RC)
 *   GPIO 25 →  PA4        TPS  (DAC1 real — reteste; cmd DAC25 <0-255>)
 *   GPIO 27 ←  PE0        INJ1
 *   GPIO 14 ←  PE2        INJ2
 *   GPIO 12 ←  PE4        INJ3
 *   GPIO 13 ←  PE6        INJ4
 *
 *   Sensores lentos por PWM+RC (saída, para o ADC do STM32; GPIO 12/13/14 são
 *   entradas do scope, não usar aqui):
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 *   GPIO 17 →  OIL        GPIO 18 →  FUEL       GPIO 16/19 →  ETB1/ETB2
 *
 *   STM32 pins are the BOARD=vgt6 map (src/hal/out_pins.h). Outputs are
 *   GPIO driven from TIM5_CH3 compare, not timer channels. IGN3 (PE13) and
 *   IGN4 (PE15) have no free ESP32 input here (GPIO25/26 are the DACs).
 *   BOARD=rgt6: INJ PA15/PB3/PC10/PC11, IGN PC6/PC7/PC8/PC9.
 *   GND     —  GND        OBRIGATÓRIO
 *
 * ── Comandos série (115200 baud) ────────────────────────────────────────────
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
static ChanDef kChan[] = {
    // IGN: GPIO assignments matching scope.ino corrected pin mapping
    { GPIO_NUM_32,  "IGN1", "PE9",  true  },   // CH0 — IGN1 (cyl 1)
    { GPIO_NUM_33,  "IGN2", "PE11", true  },   // CH1 — IGN2 (cyl 2)
    { GPIO_NUM_25,  "IGN3", "PE13", false },   // CH2 — disabled (GPIO25 = TPS DAC1)
    { GPIO_NUM_26,  "IGN4", "PE15", false },   // CH3 — disabled (GPIO26 = MAP DAC2)
    // INJ: GPIO assignments matching scope.ino corrected pin mapping
    { GPIO_NUM_27,  "INJ1", "PE0",  true  },   // CH4 — INJ1 (cyl 1)
    { GPIO_NUM_14,  "INJ2", "PE2",  true  },   // CH5 — INJ2 (cyl 2)
    { GPIO_NUM_12,  "INJ3", "PE4",  true  },   // CH6 — INJ3 (cyl 3)
    { GPIO_NUM_13,  "INJ4", "PE6",  true  },   // CH7 — INJ4 (cyl 4)
    // CKP/CMP: CKP via GPIO34 loopback, CMP virtual
    { CKP_LB_GPIO,  "CKP",  "PA0",  true  },   // CH8 — loopback real do RMT
    { kVirtual,     "CMP",  "PA1",  true  },   // CH9 — virtual (software)
};
static constexpr int kNChan = (int)(sizeof(kChan) / sizeof(kChan[0]));
static constexpr int kCkpChan = 8;  // índice do canal CKP
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// (tido como danificado na era do stimulator antigo — comando DAC25 <0-255>
// permite medir o pino cru com multímetro; se confirmar morto, TPS volta a
// PWM no GPIO21, liberado pelo MAP).
// Cablagem: GPIO26→PA3(MAP, direto), GPIO25→PA4(TPS, direto).

struct SimState {
    uint32_t rpm;
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}

#include "driver/dac.h"
static constexpr dac_channel_t kMapDac = DAC_CHANNEL_2;  // GPIO26 → PA3
static constexpr dac_channel_t kTpsDac = DAC_CHANNEL_1;  // GPIO25 → PA4 (reteste)
static void dac_init_map_tps() {
    dac_output_enable(kMapDac);
    dac_output_enable(kTpsDac);
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
// LEDC PWM: 12-bit, 19 kHz, timer 0 (ch0-6): CLT,IAT,APP,OIL,FUEL,ETB1,ETB2.
// MAP e TPS não passam por aqui: usam o DAC real (dac_init_map_tps).
// Nenhum GPIO daqui pode estar em kChan (scope): GPIO12/13/14 são INJ3/INJ4/INJ2.
static constexpr int      kPwmBits = 12;
static constexpr uint32_t kPwmFreq = 19000;

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        const float pw   = m.pw_us    / 1000.0f;
        const float per  = m.period_us / 1000.0f;
        const float freq = (m.period_us > 0) ? 1e6f / m.period_us : 0.0f;
        const char* src  = (ch == kCkpChan) ? "PA0*" : kChan[ch].pin;
        Serial.printf("│%2d│%-6s│%-7s│%8.3f│%8.3f│%8.2f│%7lu│%s│\n",
                      ch, kChan[ch].name, src,
                      pw, per, freq, m.pulse_count,
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
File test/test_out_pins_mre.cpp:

/**
 * @file test/test_out_pins_mre.cpp
 * MRE (microRusEFI copper) INJ/IGN BSRR — make host-test-mre.
 *
 * INJ PE14/13/12/11 · IGN PD12/13/14/15 · EN PD11/PD10
 * docs/hw/pinout_mre_bringup.md
 */
#include "test/harness.h"

#include <cstdint>
#include <cstdio>

#include "engine/ecu_sched.h"
#include "hal/out_pins.h"

namespace {

constexpr uint8_t kPortD = 3u;
constexpr uint8_t kPortE = 4u;

void check_ch(uint8_t channel, uint8_t port, uint8_t pin, const char* hi,
              const char* lo) {
    using namespace ems::hal;
    out_pins_test_reset_stubs();
    out_pin_write(channel, 1u);
    CHECK_EQ(out_pins_test_bsrr_snapshot(port) & (1u << pin), (1u << pin), hi);
    out_pin_write(channel, 0u);
    CHECK_EQ(out_pins_test_bsrr_snapshot(port) & (1u << (pin + 16u)),
             (1u << (pin + 16u)), lo);
}

void test_out_pins_bsrr_mre(void) {
    section("out_pins: MRE BSRR (INJ PE14-11, IGN PD12-15)");
    using namespace ems::hal;

    check_ch(ECU_CH_INJ1, kPortE, 14u, "INJ1 high PE14", "INJ1 low PE14");
    check_ch(ECU_CH_INJ2, kPortE, 13u, "INJ2 high PE13", "INJ2 low PE13");
    check_ch(ECU_CH_INJ3, kPortE, 12u, "INJ3 high PE12", "INJ3 low PE12");
    check_ch(ECU_CH_INJ4, kPortE, 11u, "INJ4 high PE11", "INJ4 low PE11");
    check_ch(ECU_CH_IGN1, kPortD, 12u, "IGN1 high PD12", "IGN1 low PD12");
    check_ch(ECU_CH_IGN2, kPortD, 13u, "IGN2 high PD13", "IGN2 low PD13");
    check_ch(ECU_CH_IGN3, kPortD, 14u, "IGN3 high PD14", "IGN3 low PD14");
    check_ch(ECU_CH_IGN4, kPortD, 15u, "IGN4 high PD15", "IGN4 low PD15");

    out_pins_test_reset_stubs();
    out_pins_hw_init();
    const uint32_t e = out_pins_test_bsrr_snapshot(kPortE);
    const uint32_t d = out_pins_test_bsrr_snapshot(kPortD);
    const uint8_t pe_safe[] = {11u, 12u, 13u, 14u};
    for (uint8_t i = 0u; i < 4u; ++i) {
        const uint8_t pin = pe_safe[i];
        char msg[48];
        std::snprintf(msg, sizeof(msg), "safe-early: PE%u reset", pin);
        CHECK_TRUE((e & (1u << (pin + 16u))) != 0u, msg);
    }
    const uint8_t pd_safe[] = {10u, 11u, 12u, 13u, 14u, 15u};
    for (uint8_t i = 0u; i < 6u; ++i) {
        const uint8_t pin = pd_safe[i];
        char msg[48];
        std::snprintf(msg, sizeof(msg), "safe-early: PD%u reset", pin);
        CHECK_TRUE((d & (1u << (pin + 16u))) != 0u, msg);
    }

    out_pins_test_reset_stubs();
    power_stage_enable(true);
    CHECK_TRUE((out_pins_test_bsrr_snapshot(kPortD) & ((1u << 10u) | (1u << 11u)))
                   == ((1u << 10u) | (1u << 11u)),
               "power_stage_enable high → PD10|PD11 set");
    power_stage_enable(false);
    CHECK_TRUE((out_pins_test_bsrr_snapshot(kPortD)
                & ((1u << (10u + 16u)) | (1u << (11u + 16u))))
                   != 0u,
               "power_stage_enable low → PD10|PD11 reset");
}

}  // namespace

int main(void) {
    printf("OpenEMS MRE out_pins Tests\n");
    printf("============================================================\n");
    test_out_pins_bsrr_mre();
    printf("\n============================================================\n");
    printf("MRE out_pins: %d passed, %d failed\n", g_pass, g_fail);
    return g_fail ? 1 : 0;
}

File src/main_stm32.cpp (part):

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    system_stm32_init();

    // 1a) CRITICAL: INJ/IGN LOW before any delay.
    // PA15 resets as JTDI with pull-up → HIGH → injectors on (active-high).
    // PC10/11 float; external pull-ups can also pull INJ high.
    // Must run before the USB 300 ms wait (was: ECU_Hardware_Init after that).
    ::ecu_sched_outputs_safe_early();
    // ETB (ponte H), ventoinha e bomba: LOW antes de qualquer espera (flutuam após o reset).
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    // Com SysTick já configurado em system_stm32_init(), é seguro habilitar aqui.
    __asm__ volatile("cpsie i" ::: "memory");

    // 1c) PB2 (LED WeAct) como saída — heartbeat visível desde o boot.
    GPIOB_MODER = (GPIOB_MODER & ~(3u << 4u)) | (1u << 4u);

    // 1d) USB CDC CEDO: só depende de clock (HSI48/CRS já prontos) + IRQs. Subir aqui,
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    ems::hal::adc_init();
    iwdg_kick();

    // 4) CAN + bench communication. MVP transport: USART1 PA9/PA10.
    // (usb_cdc_init() já foi chamado cedo em 1b, antes dos inits da ECU.)
    ems::hal::can0_init();
    ems::hal::uart0_init(115200u);
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    ems::hal::flex_fuel_init();
    ems::hal::ac_request_init();
#if EMS_BOARD_IS_VGT6
    // Datalog no SD (SDMMC1 em PC8..PC12/PD2: só livre na VGT6). Não bloqueia: o cartão é
    // identificado aos poucos por sd_poll(); sem cartão o log fica OFF e nada mais muda.
    ems::hal::sd_init();
    ems::app::datalog_init();
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            }
        }

        // ── 500ms: agenda flush Flash + LED heartbeat (PB2 WeAct blue LED) ─
        // PB2 = LED blue on-board da WeAct STM32H562 LQFP100.
        // FIX P0: Only allow flash writes when engine is stopped or below safe RPM
        static bool adaptive_flush_pending = false;
        ems::hal::nvm_set_now_ms(now);
        if (elapsed(now, g_t500ms_, 500u)) {
            g_t500ms_ = now;
            // LED heartbeat: toggle PB2 a cada 500ms (1 Hz)
            GPIOB_MODER = (GPIOB_MODER & ~(3u << 4u)) | (1u << 4u);
            GPIOB_ODR ^= (1u << 2u);  // toggle PB2
            const auto snap = ems::drv::ckp_snapshot();
            // FIX: gate ALL flash writes behind the same RPM threshold — calibration
            // writes had no RPM check, creating a latent bug (see Blocker #3).
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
